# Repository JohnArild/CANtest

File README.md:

# CANtest

This project is created to test CAN functionality on STM32
For initial testing, STM32F103C8T6 (Blue Pill) was used.
New board is designed and ordered with STM32F042F6P6. (found in folder kiCad.)

Code is still a mess and just for testing.

Released under BSD License, see file named LICENSE

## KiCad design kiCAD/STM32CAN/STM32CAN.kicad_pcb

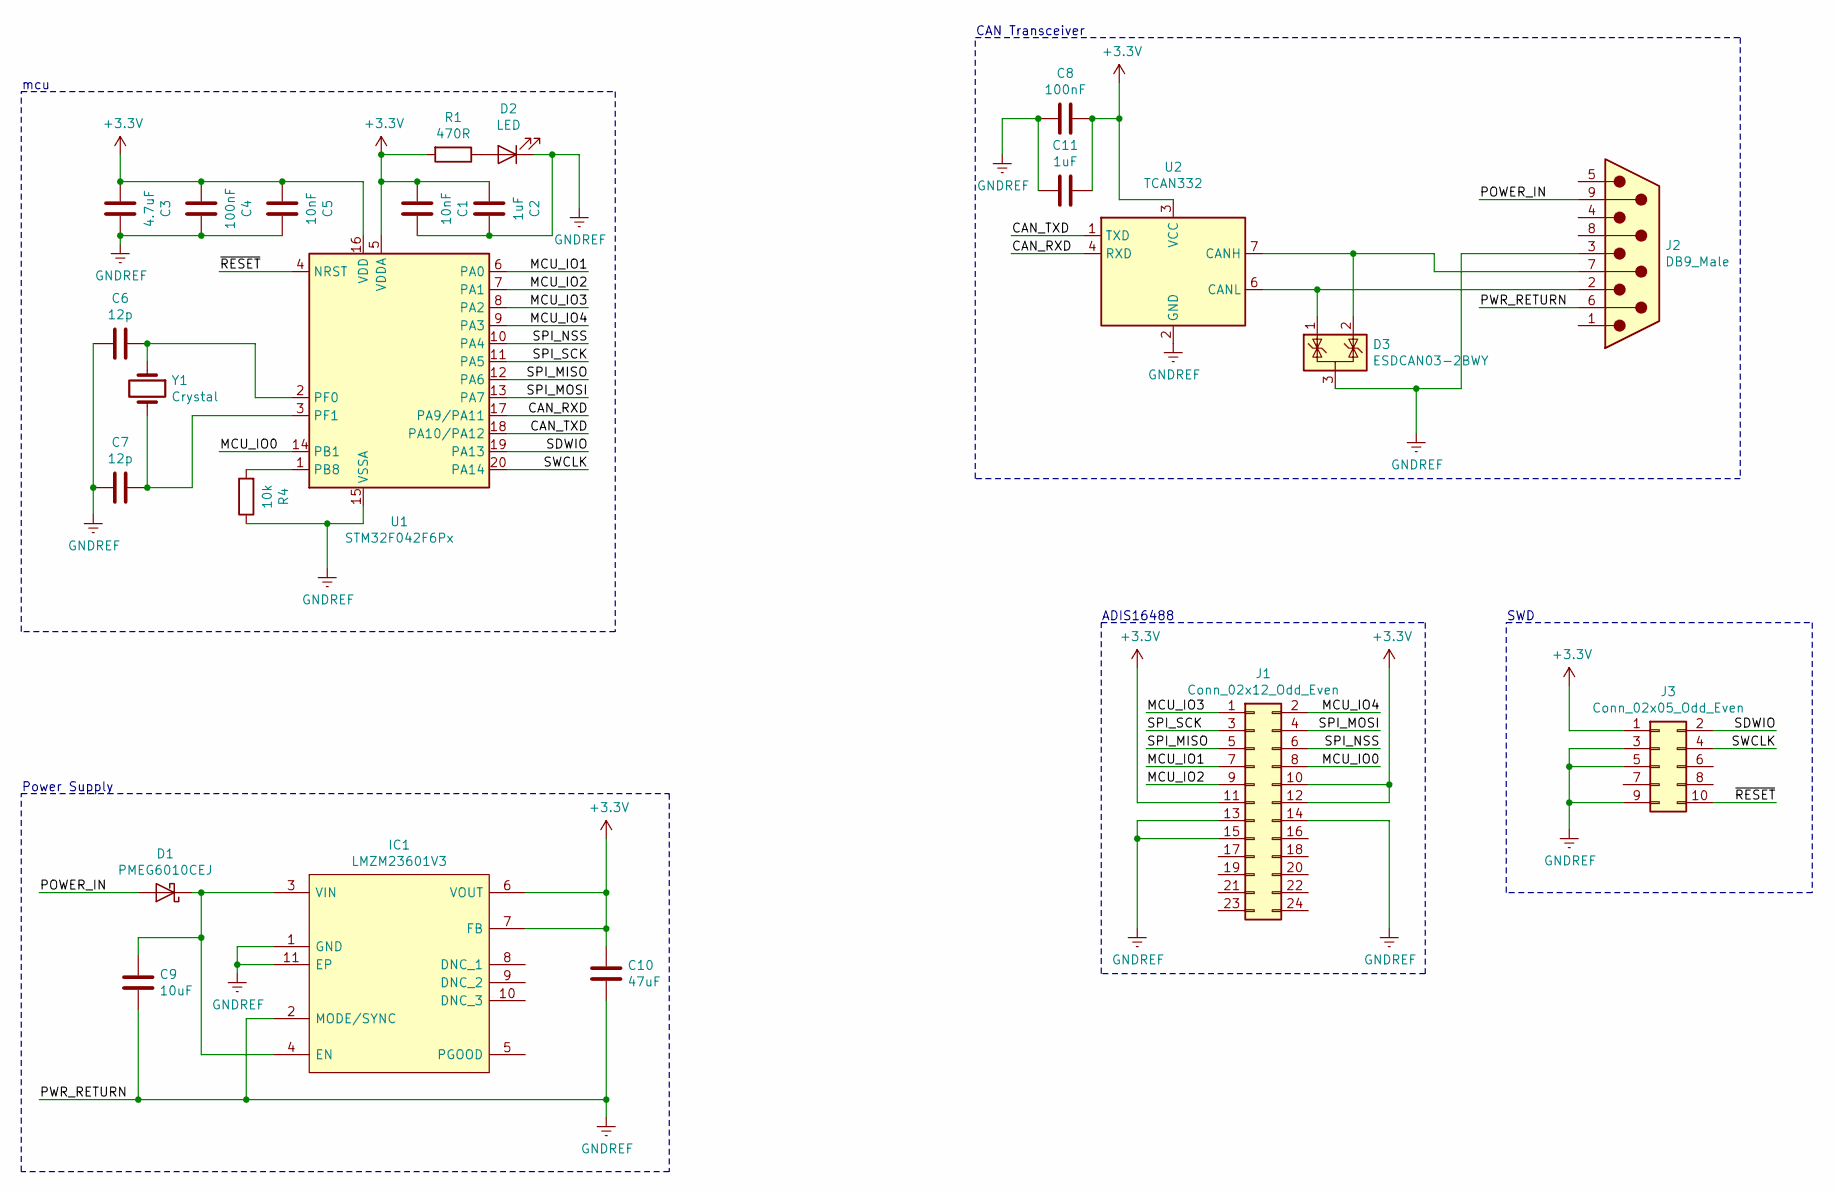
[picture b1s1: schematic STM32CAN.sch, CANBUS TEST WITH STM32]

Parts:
C1, C5: 10nF; C_0603_1608Metric
C2, C11: 1uF; C_0603_1608Metric
C3: 4.7uF; C_0603_1608Metric
C4, C8: 100nF; C_0603_1608Metric
C6, C7: 12p; C_0603_1608Metric
C9: 10uF; C_0805_2012Metric
C10: 47uF; C_1206_3216Metric
D1: PMEG6010CEJ; D_SOD-323
D2: LED; D_0603_1608Metric
D3: ESDCAN03-2BWY; SOT-323_SC-70
IC1: LMZM23601V3; LMZM23601V5SILR; Mouser Part Number 595-LMZM23601V5SILT
J1: Conn_02x12_Odd_Even; PinHeader_2x12_P1.27mm_Vertical_SMD
J2: DB9_Male; DSUB-9_Male_Horizontal_P2.77x2.54mm_EdgePinOffset9.40mm
J3: Conn_02x05_Odd_Even; PinHeader_2x05_P1.27mm_Vertical_SMD
R1: 470R; R_0603_1608Metric
R4: 10k; R_0603_1608Metric
U1: STM32F042F6Px; TSSOP-20_4.4x6.5mm_P0.65mm
U2: TCAN332; SOIC-8_3.9x4.9mm_P1.27mm
Y1: Crystal; 7A8000MAAET

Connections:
+3V3: C1.2, C2.2, C3.2, C4.2, C5.2, C8.1, C10.1, C11.1, IC1.6 (VOUT), IC1.7 (FB), J1.10, J1.11, J1.12, J3.1, R1.2, U1.5 (VDDA), U1.16 (VDD), U2.3 (VCC)
/CAN_RXD: U1.17 (PA9/PA11), U2.4 (RXD)
/CAN_TXD: U1.18 (PA10/PA12), U2.1 (TXD)
/MCU_IO0: J1.8, U1.14 (PB1)
/MCU_IO1: J1.7, U1.6 (PA0)
/MCU_IO2: J1.9, U1.7 (PA1)
/MCU_IO3: J1.1, U1.8 (PA2)
/MCU_IO4: J1.2, U1.9 (PA3)
/POWER_IN: D1.2 (A), J2.9
/SDWIO: J3.2, U1.19 (PA13)
/SPI_MISO: J1.5, U1.12 (PA6)
/SPI_MOSI: J1.4, U1.13 (PA7)
/SPI_NSS: J1.6, U1.10 (PA4)
/SPI_SCK: J1.3, U1.11 (PA5)
/SWCLK: J3.4, U1.20 (PA14)
/~RESET: J3.10, U1.4 (NRST)
GNDREF: C1.1, C2.1, C3.1, C4.1, C5.1, C6.2, C7.2, C8.2, C9.2, C10.2, C11.2, D2.1 (K), D3.3 (A), IC1.1 (GND), IC1.2 (MODE/SYNC), IC1.11 (EP), J1.13, J1.14, J1.15, J2.3, J2.6, J3.3, J3.5, J3.9, R4.1, U1.15 (VSSA), U2.2 (GND); also elsewhere on the board
unnamed: C6.1, U1.2 (PF0), Y1.1
unnamed: C7.1, U1.3 (PF1), Y1.2
unnamed: C9.1, D1.1 (K), IC1.3 (VIN), IC1.4 (EN)
unnamed: D2.2 (A), R1.1
unnamed: D3.1 (K), J2.2, U2.6 (CANL)
unnamed: D3.2 (K), J2.7, U2.7 (CANH)
unnamed: R4.2, U1.1 (PB8)

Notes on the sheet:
mcu
ADIS16488
SWD
CAN Transceiver
Power Supply

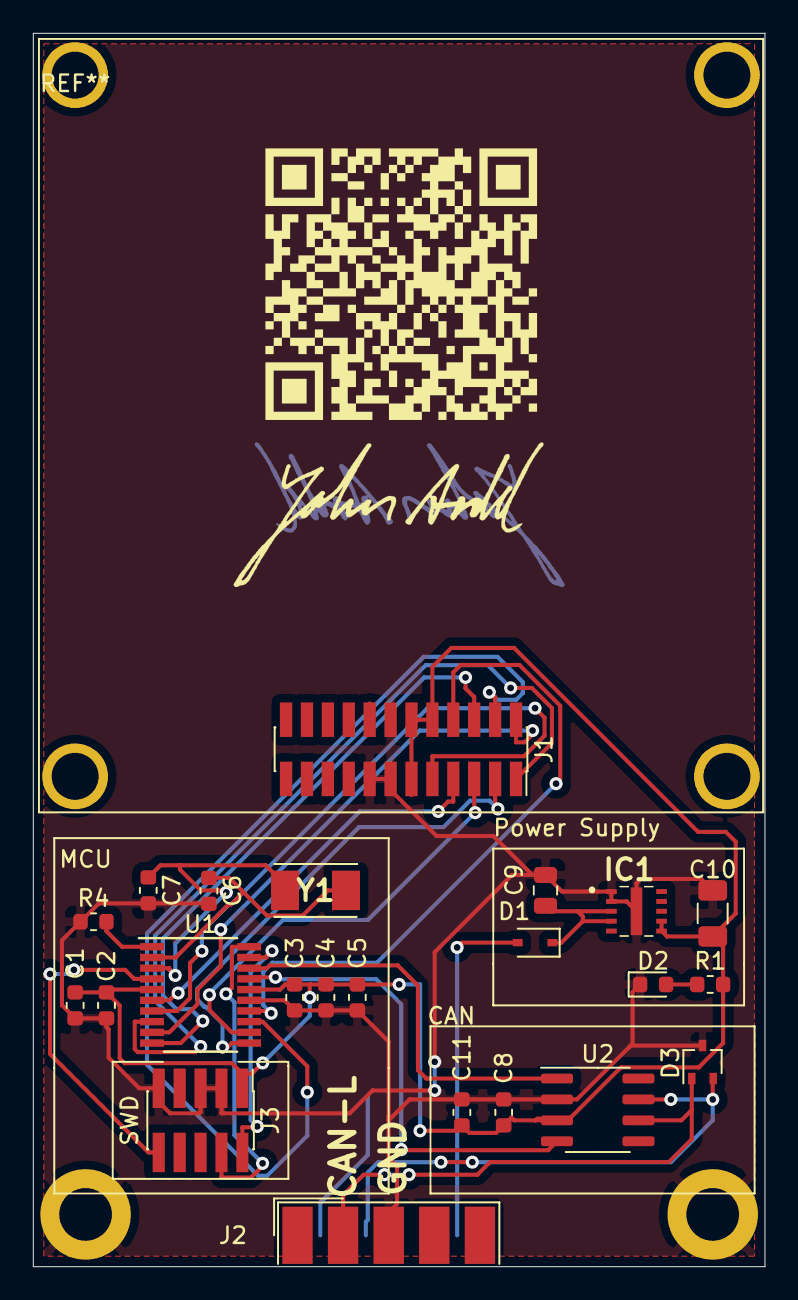
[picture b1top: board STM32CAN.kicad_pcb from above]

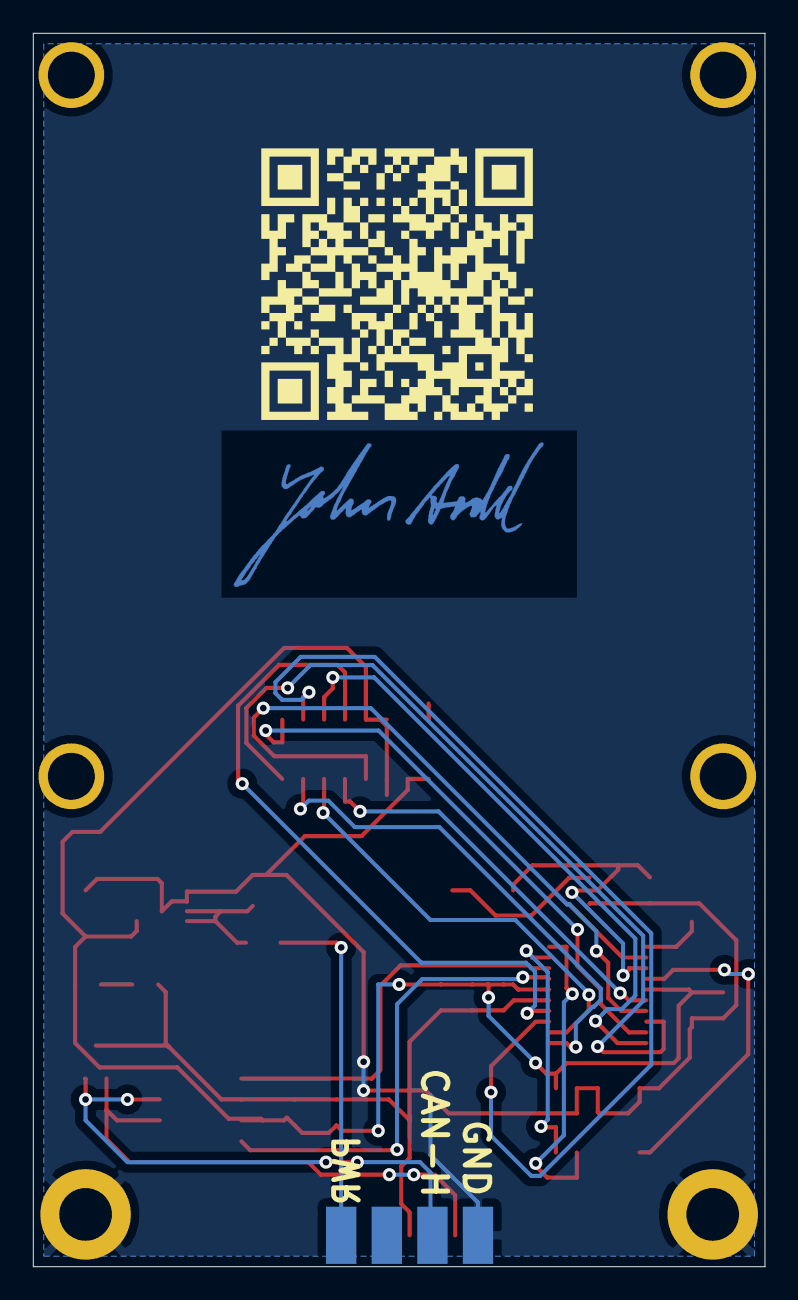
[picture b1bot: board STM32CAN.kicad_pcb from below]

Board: 2 copper layers, 44.5 x 74.9 mm, 29 parts (2 on the bottom side), 24 nets.

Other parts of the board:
GG1: LOGO; sign-small-Cu
GG2: LOGO; sign-small
Pad1, Pad2: MountingHole_3.2mm_M3_ISO14580_Pad
QR1, QR2: QR_CANtest

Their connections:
GNDREF: Pad1.GNDREF, Pad2.GNDREF; also elsewhere on the board

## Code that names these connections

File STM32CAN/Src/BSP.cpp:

/**
  ******************************************************************************
  * @file    BSP.cpp
  * @author  John Arild Lolland
  ******************************************************************************
*/

#include "BSP.h"

int BSP_STM32CAN::initilize (){
    BSP_STM32CAN::MCUspeed_48MHz();
	BSP_STM32CAN::setup_GPIO ();
	BSP_STM32CAN::setup_CAN ();
	BSP_STM32CAN::setup_SPI ();
    return 0;
}

int BSP_STM32CAN::MCUspeed_48MHz (){
	FLASH->ACR |= FLASH_ACR_LATENCY; // One wait-state for 48MHz operation
	FLASH->ACR |= FLASH_ACR_PRFTBE; // Prefetch buffer enable
	RCC->AHBENR |= RCC_AHBENR_GPIOFEN; // External crystal is on Port F
	RCC->CFGR |= RCC_CFGR_PLLMUL6; // Set PLL to x6 for 48MHz
	RCC->CFGR |= RCC_CFGR_PLLSRC_HSE_PREDIV; // HSE/PREDIV selected as PLL input clock
	RCC->CR |= RCC_CR_HSEON; // Turn in external clock input
	while(!((RCC->CR & RCC_CR_HSERDY)== RCC_CR_HSERDY)){;} // wait for HSE to be ready
	RCC->CR |= RCC_CR_PLLON;
	while(!((RCC->CR & RCC_CR_PLLRDY)== RCC_CR_PLLRDY)){;} // wait for PLL to be ready
	RCC->CFGR |= RCC_CFGR_SW_PLL; // Select PLL for SYSCLOCK
    return 0;
}

int BSP_STM32CAN::setup_GPIO (){
	//Enable ports
	RCC->AHBENR |= RCC_AHBENR_GPIOAEN;
	RCC->AHBENR |= RCC_AHBENR_GPIOBEN;

	//Set up IO pins
	GPIOB->MODER |= GPIO_MODER_MODER1_0; // MCU_IO0 (output)
	GPIOA->MODER |= GPIO_MODER_MODER0_0; // MCU_IO1 (output)
	GPIOA->MODER |= GPIO_MODER_MODER1_0; // MCU_IO2 (output)
	GPIOA->MODER |= GPIO_MODER_MODER2_0; // MCU_IO3 (output)
	GPIOA->MODER |= GPIO_MODER_MODER3_0; // MCU_IO4 (output)
    return 0;
}

int BSP_STM32CAN::setup_CAN (){
	RCC->AHBENR |= RCC_AHBENR_GPIOAEN;
	RCC->APB2ENR |= RCC_APB2ENR_SYSCFGCOMPEN;
	SYSCFG->CFGR1 |= SYSCFG_CFGR1_PA11_PA12_RMP; // Remap (pin pair PA11/12 mapped instead of PA9/10)
	GPIOA->MODER |= GPIO_MODER_MODER11_1; // CAN_RXD (alternative)
	GPIOA->MODER |= GPIO_MODER_MODER12_1; // CAN_TXD (alternative)
	GPIOA->AFR[1] |= 0x44000U; // Set Port 11 and 12 as AF4 for CAN
	//GPIOA->OTYPER |= GPIO_OTYPER_OT_11;
	//GPIOA->OTYPER |= GPIO_OTYPER_OT_12;
	GPIOA->OSPEEDR |= GPIO_OSPEEDR_OSPEEDR11_0 |GPIO_OSPEEDR_OSPEEDR11_1;
	GPIOA->OSPEEDR |= GPIO_OSPEEDR_OSPEEDR12_0 |GPIO_OSPEEDR_OSPEEDR12_1;
	GPIOA->PUPDR |= GPIO_PUPDR_PUPDR11_0;
	GPIOA->PUPDR |= GPIO_PUPDR_PUPDR12_0;
	RCC->APB1ENR |= RCC_APB1ENR_CANEN;
	CAN->MCR |= CAN_MCR_INRQ; // Initialization Request
	//CAN->BTR |= CAN_BTR_LBKM; // Debug mode
	//CAN->MCR |= CAN_MCR_NART; // No retransmitt

	//Create CAN message for testing:
	uint16_t CAN_ID = 0x123;
	uint32_t TIxR = 0;
	TIxR = (CAN_ID << 21); // move 11bit ID to bit 21-31
	while(!((CAN->MSR & CAN_MSR_INAK) == CAN_MSR_INAK)){;} // Wait for INAK to become ready
	CAN->MCR &= ~(0x00010000); // Let CAN work in debug mode
	CAN->MCR &= ~(CAN_MCR_SLEEP); // Wake CAN
	CAN->MCR |= CAN_MCR_TXFP; // Transmit FIFO priority
	CAN->sTxMailBox[0].TDTR |= 0x4;
	CAN->sTxMailBox[0].TIR = TIxR;
	uint32_t CAN_Data = 0xDEADBEEF;
	CAN->sTxMailBox[0].TDLR = CAN_Data;
	CAN->MCR &= ~(CAN_MCR_INRQ);
	CAN->sTxMailBox[0].TIR |= CAN_TI0R_TXRQ;
    return 0;
}

int BSP_STM32CAN::setup_SPI (){
	RCC->AHBENR |= RCC_AHBENR_GPIOAEN;
	GPIOA->MODER |= GPIO_MODER_MODER4_1; // SPI_NSS (alternative)
	GPIOA->MODER |= GPIO_MODER_MODER5_1; // SPI_SCK (alternative)
	GPIOA->MODER |= GPIO_MODER_MODER6_1; // SPI_MISO (alternative)
	GPIOA->MODER |= GPIO_MODER_MODER7_1; // SPI_MOSI (alternative)
	RCC->APB2ENR |= RCC_APB2ENR_SPI1EN;
    return 0;
}

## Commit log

2019-06-05 Changed to STM32CubeIDE
2019-06-05 added metadata
2019-06-05 Changed SYSCLK to 48MHz Added README.md and LICENSE Added vscode workspace files
2019-06-08 Added some GPIO settings for CAN IO
2019-06-08 CAN is now sending message
2019-06-10 added KiCAD files
2019-06-15 Updated kiCAD drawing
2019-06-16 Started layout
2019-06-16 Rev.- complete. Board ordered
2019-06-21 Added render of PCB
2019-06-21 test
2019-06-21 Added PCB info
2019-06-27 Added BSP class Not yet implemented
2019-07-22 cloeard main
2019-07-29 Blinky light works at 48MHz PLL from HSE with STM32CAN-Board
2019-07-30 CAN on GPIOA doing something now.
